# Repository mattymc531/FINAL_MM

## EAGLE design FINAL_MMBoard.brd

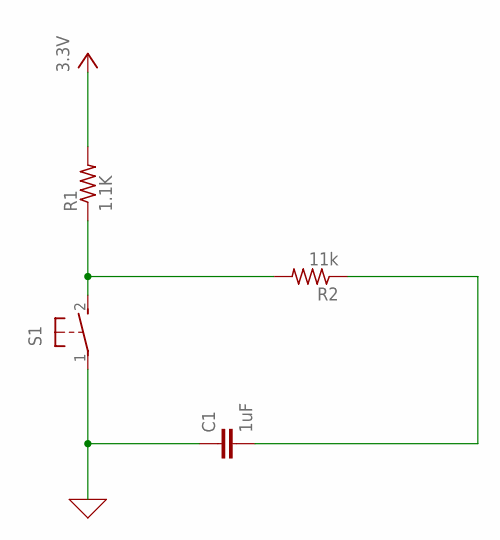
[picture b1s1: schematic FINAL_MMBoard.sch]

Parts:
C1: 1uF; C2.5-3
R1: 1.1K; 0204V
R2: 11k; 0204V
S1: 31-XX; B3F-31XX

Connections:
0: C1.1, S1.1
unnamed: R1.1, R2.2, S1.2 (S)
unnamed: C1.2, R2.1
VCC: R1.2

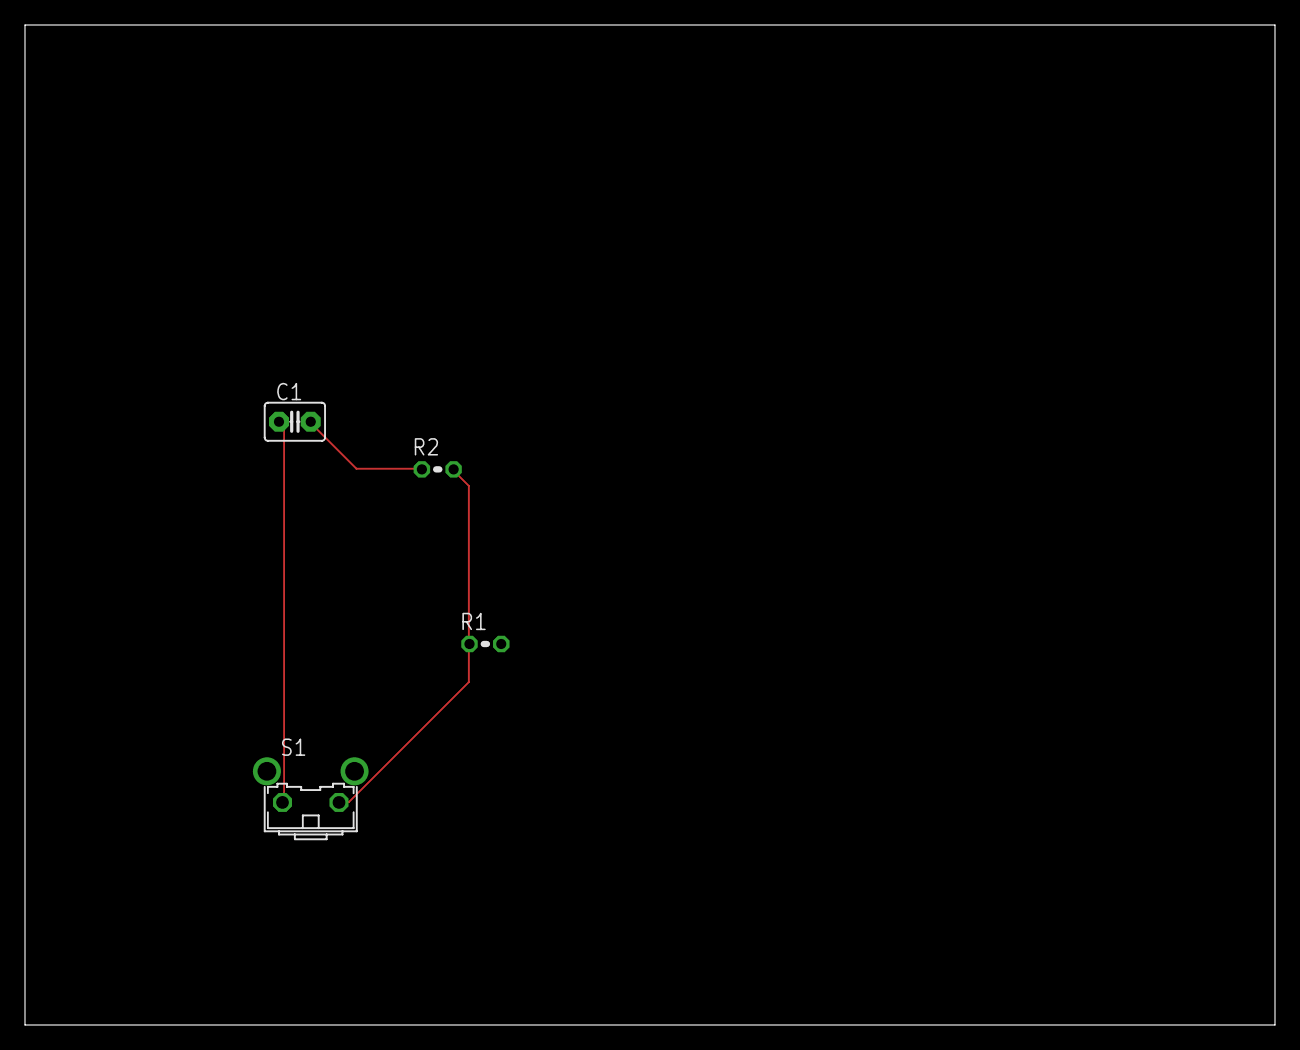
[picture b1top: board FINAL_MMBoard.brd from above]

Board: 2 copper layers, 100.0 x 80.0 mm, 4 parts (0 on the bottom side), 3 nets.
